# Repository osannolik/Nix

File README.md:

# Yet another nixie tube clock

- IN-14 tubes
- DC3234 RTC keeps the time
- Software written in Rust running on STM32L0
- Can show time or temperature sent over Bluetooth using an external BLE-SPI-bridge
- Use whatever step-up converter you want to

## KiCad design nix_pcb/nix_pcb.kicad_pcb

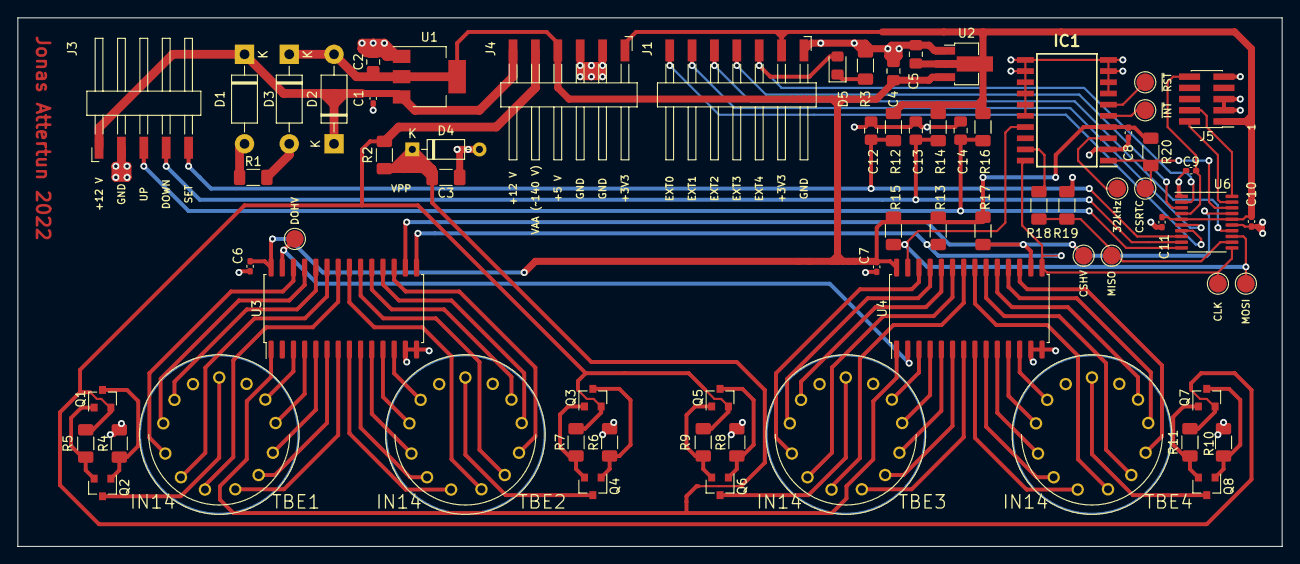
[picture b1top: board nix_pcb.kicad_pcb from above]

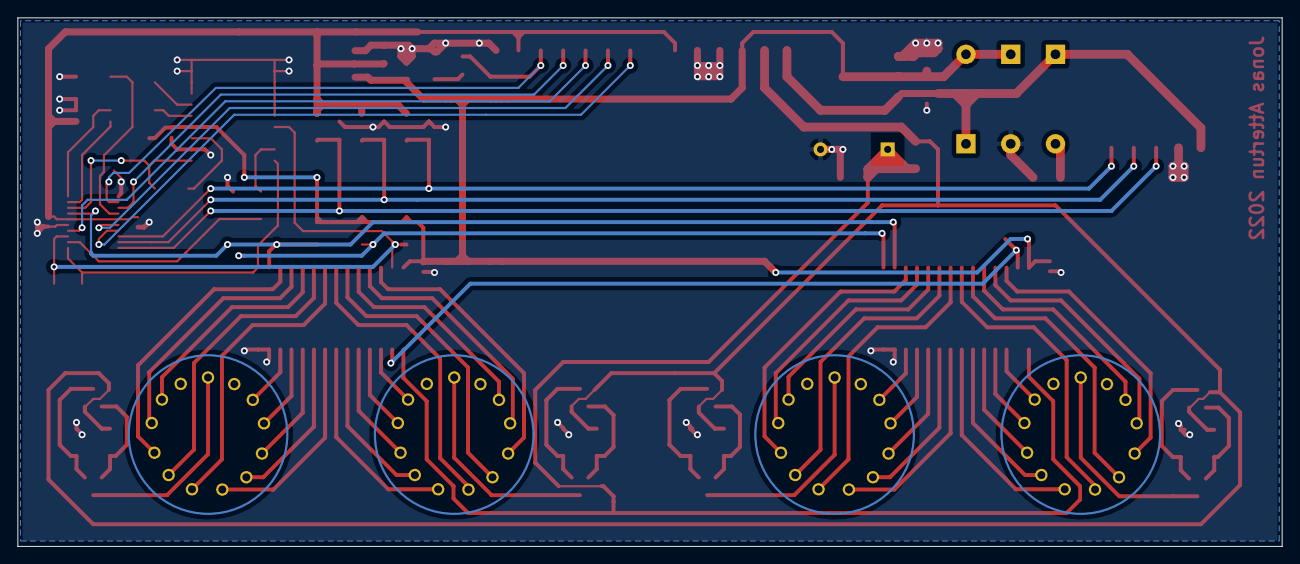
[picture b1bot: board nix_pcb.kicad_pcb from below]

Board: 2 copper layers, 143.5 x 60.0 mm, 70 parts (4 on the bottom side), 81 nets.

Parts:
C1, C6, C7, C8, C9, C10, C11: 100n; C_0402_1005Metric_Pad0.74x0.62mm_HandSolder
C2, C4, C5: 10u; C_0805_2012Metric_Pad1.18x1.45mm_HandSolder
C3: 1u; C_1206_3216Metric_Pad1.33x1.80mm_HandSolder
C12, C13, C14: C; C_0805_2012Metric_Pad1.18x1.45mm_HandSolder
D1, D2, D3: 1N5819; D_DO-41_SOD81_P10.16mm_Horizontal
D4: BZX79 75V; D_DO-35_SOD27_P7.62mm_Horizontal
D5: LED; LED_0805_2012Metric_Pad1.15x1.40mm_HandSolder
IC1: DS3234SN#; SOIC127P1032X265-20N
J1: Conn_01x07; Harwin_M20-89007xx_1x07_P2.54mm_Horizontal
J3: Conn_01x05; Harwin_M20-89005xx_1x05_P2.54mm_Horizontal
J4: Conn_01x06; Harwin_M20-89006xx_1x06_P2.54mm_Horizontal
J5: Conn_ARM_JTAG_SWD_10; PinHeader_2x05_P1.27mm_Vertical_SMD
Q1, Q2, Q3, Q4, Q5, Q6, Q7, Q8: MMBTA92; SOT-23
R1: 2k2; R_1206_3216Metric_Pad1.30x1.75mm_HandSolder
R2: 100k; R_1206_3216Metric_Pad1.30x1.75mm_HandSolder
R3, R5, R7, R9, R11: 330; R_1206_3216Metric_Pad1.30x1.75mm_HandSolder
R4, R6, R8, R10: 330k; R_1206_3216Metric_Pad1.30x1.75mm_HandSolder
R12, R13, R14, R15, R16, R17, R19, R20: 10k; R_1206_3216Metric_Pad1.30x1.75mm_HandSolder
R18: 5k6; R_1206_3216Metric_Pad1.30x1.75mm_HandSolder
TBE1, TBE2, TBE3, TBE4: IN14; IN-14-mod
TP1, TP2, TP3, TP4, TP5, TP6, TP7, TP8, TP9: TestPoint; TestPoint_Pad_D2.0mm
U1: LD1117S50TR_SOT223; SOT-223-3_TabPin2
U2: AZ1117-3.3; SOT-89-3_Handsoldering
U3, U4: HV5812; SOIC-28W_7.5x17.9mm_P1.27mm
U6: STM32L031F6Px; TSSOP-20_4.4x6.5mm_P0.65mm

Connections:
+3V3: C5.1, C10.1, C11.1, J1.2, J4.1, J5.1, R12.1, R14.1, R16.1, U2.2, U6.5, U6.16
+5V: C2.1, C4.1, C6.1, C7.1, C8.1, D2.2, D3.1, IC1.4, J4.4, R13.1, R15.1, R17.1, R20.1, U1.2, U2.3, U3.28, U4.28
+12V: C1.1, D1.1, D2.1, J3.1, J4.6, U1.3
/DOWN: C13.1, J3.4, R14.2, U6.9
/SET: C12.1, J3.5, R12.2, U6.8
/UP: C14.1, J3.3, R16.2, U6.10
/controller/Ext0: J1.7, U6.7
/controller/Ext1: J1.6, U6.6
/controller/Ext2: J1.5, U6.14
/controller/Ext3: J1.4, U6.3
/controller/Ext4: D5.2, J1.3, U6.2
/controller/HVCLOCK: IC1.20, R13.2, TP2.1, U3.15, U4.15, U6.11
/controller/HVDATA: IC1.17, R15.2, TP1.1, U4.27, U6.13
/controller/HVSTROBE: R17.2, TP3.1, U3.16, U4.16, U6.17
/controller/RTC_CS: IC1.1, R20.2, TP8.1, U6.18
/controller/RTC_DOUT: IC1.19, R18.1
/controller/SPI_MISO: R18.2, R19.1, TP9.1, U6.12
/controller/SWCLK: J5.4, U6.20
/controller/SWDIO: J5.2, U6.19
/tubes/A0: TBE1.3, U3.3
/tubes/A1: TBE1.10, U3.26
/tubes/A2: TBE1.11, U3.25
/tubes/A3: TBE1.12, U3.24
/tubes/A4: TBE1.9, U3.23
/tubes/A5: TBE1.8, U3.22
/tubes/A6: TBE1.7, U3.7
/tubes/A7: TBE1.6, U3.6
/tubes/A8: TBE1.5, U3.5
/tubes/A9: TBE1.4, U3.4
/tubes/B0: TBE2.5, U3.17
/tubes/B1: TBE2.12, U3.12
/tubes/B2: TBE2.11, U3.11
/tubes/B3: TBE2.10, U3.10
/tubes/B4: TBE2.9, U3.9
/tubes/B5: TBE2.8, U3.8
/tubes/B6: TBE2.7, U3.21
/tubes/B7: TBE2.6, U3.20
/tubes/B8: TBE2.3, U3.19
/tubes/B9: TBE2.4, U3.18
/tubes/C0: TBE3.3, U4.3
/tubes/C1: TBE3.10, U4.26
/tubes/C2: TBE3.11, U4.25
/tubes/C3: TBE3.12, U4.24
/tubes/C4: TBE3.9, U4.23
/tubes/C5: TBE3.8, U4.22
/tubes/C6: TBE3.7, U4.7
/tubes/C7: TBE3.6, U4.6
/tubes/C8: TBE3.5, U4.5
/tubes/C9: TBE3.4, U4.4
/tubes/D0: TBE4.5, U4.17
/tubes/D1: TBE4.12, U4.12
/tubes/D2: TBE4.11, U4.11
/tubes/D3: TBE4.10, U4.10
/tubes/D4: TBE4.9, U4.9
/tubes/D5: TBE4.8, U4.8
/tubes/D6: TBE4.7, U4.21
/tubes/D7: TBE4.6, U4.20
/tubes/D8: TBE4.3, U4.19
/tubes/D9: TBE4.4, U4.18
GND: C1.2, C2.2, C3.2, C4.2, C5.2, C6.2, C7.2, C8.2, C9.2, C10.2, C11.2, C12.2, C13.2, C14.2, D3.2, D4.2, IC1.2, IC1.7, IC1.8, IC1.9, IC1.10, IC1.11, IC1.12, IC1.13, IC1.14, IC1.15, IC1.16, J1.1, J3.2, J4.2, J4.3, J5.3, J5.5, J5.9, R1.2, R3.1, R4.2, R6.2, R8.2, R10.2, R19.2, U1.1, U2.1, U3.13, U3.14, U4.13, U4.14, U6.1, U6.15
unnamed: C9.1, J5.10, U6.4
unnamed: D1.2, R1.1
unnamed: D5.1, R3.2
unnamed: IC1.3, TP5.1
unnamed: IC1.5, TP6.1
unnamed: IC1.6, TP7.1
unnamed: Q1.1, Q2.2, R5.2
unnamed: Q1.3, Q2.1, R4.1
unnamed: Q2.3, TBE1.1
unnamed: Q3.1, Q4.2, R7.2
unnamed: Q3.3, Q4.1, R6.1
unnamed: Q4.3, TBE2.1
unnamed: Q5.1, Q6.2, R9.2
unnamed: Q5.3, Q6.1, R8.1
unnamed: Q6.3, TBE3.1
unnamed: Q7.1, Q8.2, R11.2
unnamed: Q7.3, Q8.1, R10.1
unnamed: Q8.3, TBE4.1
unnamed: TP4.1, U3.27, U4.2
VAA: J4.5, Q1.2, Q3.2, Q5.2, Q7.2, R2.1, R5.1, R7.1, R9.1, R11.1
VPP: C3.1, D4.1, R2.2, U3.1, U4.1

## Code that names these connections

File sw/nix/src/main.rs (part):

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    fn update(&mut self, set: &ButtonState, set_timeout: &mut Counter) {
        *self = match self {
            Mode::DisplayTime => match set.level {
                PinLevel::Falling if set.count < 5 => Mode::DisplayTemp,
                PinLevel::High if set.count > 10 => Mode::SetTime(DigitPair::Minutes),
                _ => *self,
            },
            Mode::DisplayTemp => match set.level {
                PinLevel::Falling if set.count < 5 => Mode::DisplayTime,
                _ => *self,
            },
            Mode::SetTime(digit_pair) => {
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                    Mode::DisplayTime
                } else {
                    match set.level {
                        PinLevel::Falling if set.count < 5 => {
                            match digit_pair {
                                DigitPair::Minutes => Mode::SetTime(DigitPair::Hours),
                                DigitPair::Hours => Mode::SetTime(DigitPair::Minutes),
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    let mut hv_cs = gpioa.pa9.into_open_drain_output();
    hv_cs.set_low().unwrap();

    let mut rtc_cs = gpioa.pa10.into_open_drain_output();
    rtc_cs.set_high().unwrap();

    let sck = gpioa
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        .spi((sck, miso, mosi), spi::MODE_1, 200_000.Hz(), &mut rcc);
    //let mut spi = SpiBitBanged::new(mosi, miso, sck);

    let set_pin = gpioa.pa2.into_pull_up_input();
    let dec_pin = gpioa.pa3.into_pull_up_input();
    let inc_pin = gpioa.pa4.into_pull_up_input();

    let mut set_button = ButtonState::new(&set_pin);
    let mut inc_button = ButtonState::new(&inc_pin);
    let mut dec_button = ButtonState::new(&dec_pin);

    let ext0 = gpioa.pa1.into_pull_up_input();      // CS
    let ext1 = gpioa.pa0.into_pull_up_input();      // SCK
    let ext2 = gpiob.pb1.into_pull_up_input();      // Bridge-MOSI

    let mut syscfg = SYSCFG::new(dp.SYSCFG, &mut rcc);
    let mut exti = Exti::new(dp.EXTI);
    let line = GpioLine::from_raw_line(ext1.pin_number()).unwrap();
    exti.listen_gpio(&mut syscfg, ext1.port(), line, TriggerEdge::Rising);


    //let mut btn = ButtonState2::new();
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
        //btn.update(&button_set, &button_inc, &button_dec);

        set_button.update(&set_pin);
        inc_button.update(&inc_pin);
        dec_button.update(&dec_pin);

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
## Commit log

2022-01-26 first ds3234 design
2022-01-29 removed button board
2022-01-29 add gnd to ext-conn and add silkscreen text to connectors
2022-01-29 add margin to vaa pin of zener
2022-01-29 Create LICENSE
2022-10-11 some sw
2022-11-08 Add a backplate draft
2022-11-10 Adjustments and text to backplate
2022-11-10 Ordered backplate
2022-12-11 Alpha needs refactoring
2022-12-11 reset seconds when setting minutes and hours
2023-02-09 Add initial ble to spi bridge sw
2023-02-16 Write manufacturer data to spi
2023-03-03 exti test
2023-06-09 Add RTIC-version
2023-06-18 Use much slower SPI clock for ble-spi bridge - soft-spi since lowest allowed by hw is still too fast.
2023-06-18 Show nothing if BCD is out of range >9
2023-06-18 Adjust optimization
2023-06-18 Fix out of range bcd in time
2023-06-19 Add external temperature mode
2023-06-19 Show temperature from ext - forced to use software spi...
2023-06-21 Rename ext-pins
2023-06-21 Move peripheral stuff to separate file
2023-06-21 Add cargo target config
2023-06-21 Refactor to hide some interrupt handling
2023-06-21 Simplify and let External decide how to present the data
2023-06-21 Ignore unused
2023-06-21 Remove non-rtic-version of software
2023-07-08 add nrf sdk
2023-07-08 remove DS-crap
2023-07-08 pcb outputs
2023-07-08 readme and image
